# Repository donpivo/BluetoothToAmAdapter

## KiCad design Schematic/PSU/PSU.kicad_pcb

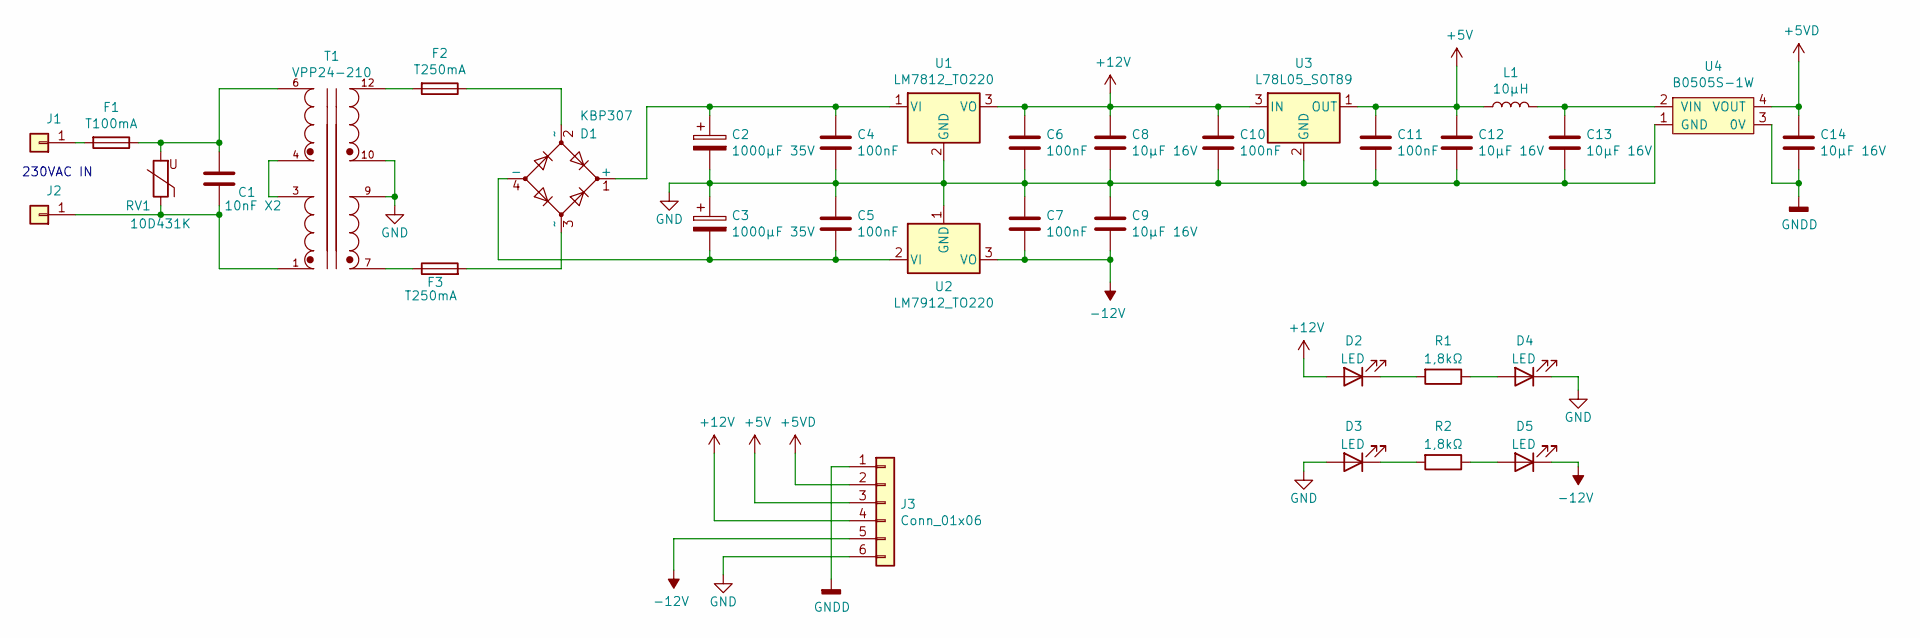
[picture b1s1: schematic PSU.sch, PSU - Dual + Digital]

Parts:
C1: 10nF X2; C_Rect_L10.3mm_W4.5mm_P7.50mm_MKS4
C2, C3: 1000µF 35V; CP_Radial_D12.5mm_P5.00mm
C4, C5, C6, C7, C10, C11: 100nF; C_0805_2012Metric_Pad1.18x1.45mm_HandSolder
C8, C9, C12, C13, C14: 10µF 16V; C_0805_2012Metric_Pad1.18x1.45mm_HandSolder
D1: KBP307; Rectifier_KBP307
D2, D3, D4, D5: LED; LED_0805_2012Metric_Pad1.15x1.40mm_HandSolder
F1: T100mA; Fuse_Littelfuse_372_D8.50mm
F2, F3: T250mA; Fuse_Littelfuse_372_D8.50mm
J1, J2: Conn_01x01; Pad_7mm
J3: Conn_01x06; KF2510-6P
L1: 10µH; L_0805_2012Metric_Pad1.15x1.40mm_HandSolder
R1, R2: 1,8kΩ; R_0805_2012Metric_Pad1.20x1.40mm_HandSolder
RV1: 10D431K; RV_Disc_D12mm_W4.3mm_P7.5mm
T1: VPP24-210; Transformer_XFMR_VPP24-210
U1: LM7812_TO220; TO-220-3_Heatsink1
U2: LM7912_TO220; TO-220-3_Heatsink1
U3: L78L05_SOT89; SOT-89-3
U4: B0505S-1W; B0505S

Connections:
+5V: C11.1, C12.1, J3.3, L1.1, U3.1 (OUT)
+5VD: C14.1, J3.2, U4.4 (VOUT)
+12V: C6.1, C8.1, C10.1, D2.2 (A), J3.4, U1.3 (VO), U3.3 (IN)
-12V: C7.2, C9.2, D5.1 (K), J3.5, U2.3 (VO)
GND: C2.2, C3.1, C4.2, C5.1, C6.2, C7.1, C8.2, C9.1, C10.2, C11.2, C12.2, C13.2, D3.2 (A), D4.1 (K), J3.6, T1.9, T1.10, U1.2 (GND), U2.1 (GND), U3.2 (GND), U4.1 (GND)
GNDD: C14.2, J3.1, U4.3 (0V)
unnamed: C1.1, F1.1, RV1.2, T1.6
unnamed: C1.2, J2.1, RV1.1, T1.1
unnamed: C2.1, C4.1, D1.1 (+), U1.1 (VI)
unnamed: C3.2, C5.2, D1.4 (-), U2.2 (VI)
unnamed: C13.1, L1.2, U4.2 (VIN)
unnamed: D1.2 (~~), F2.1
unnamed: D1.3 (~~), F3.2
unnamed: D2.1 (K), R1.2
unnamed: D3.1 (K), R2.2
unnamed: D4.2 (A), R1.1
unnamed: D5.2 (A), R2.1
unnamed: F1.2, J1.1
unnamed: F2.2, T1.12
unnamed: F3.1, T1.7
unnamed: T1.3, T1.4

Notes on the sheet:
230VAC IN

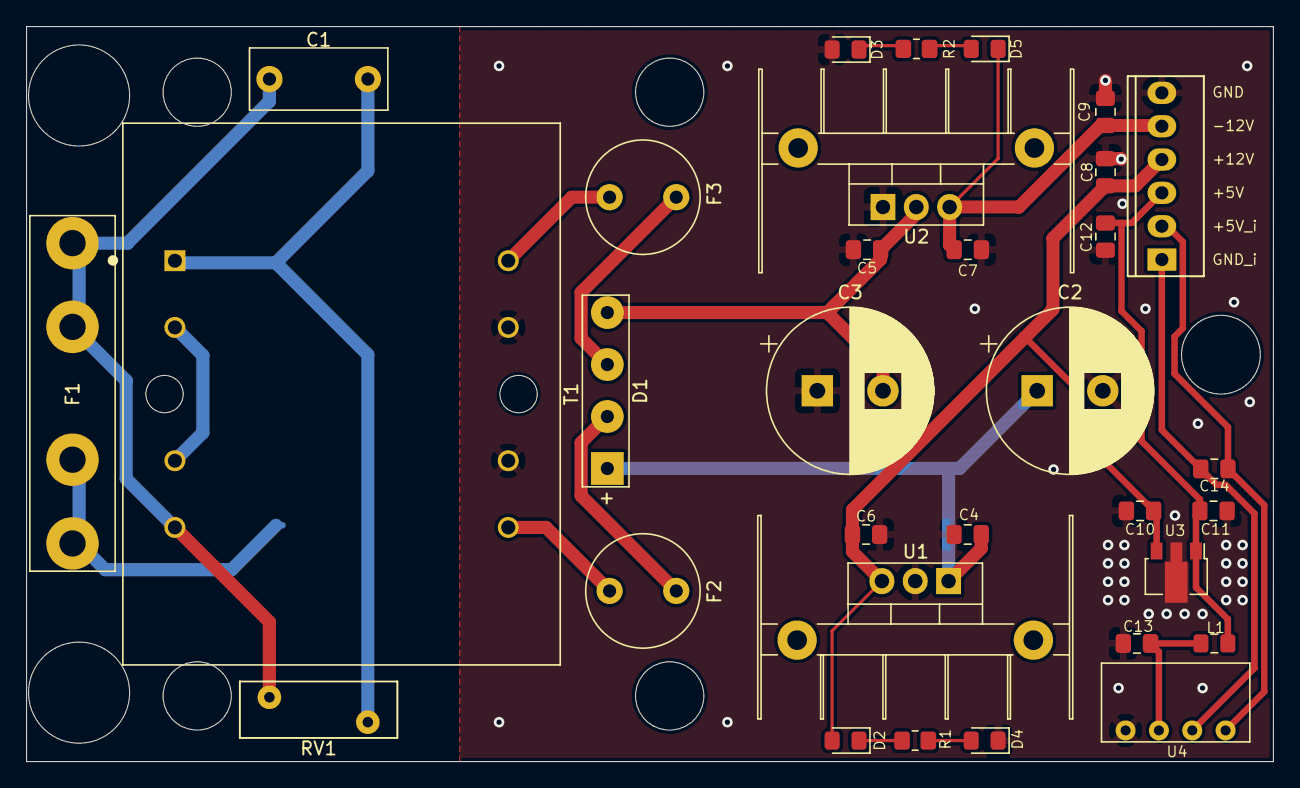
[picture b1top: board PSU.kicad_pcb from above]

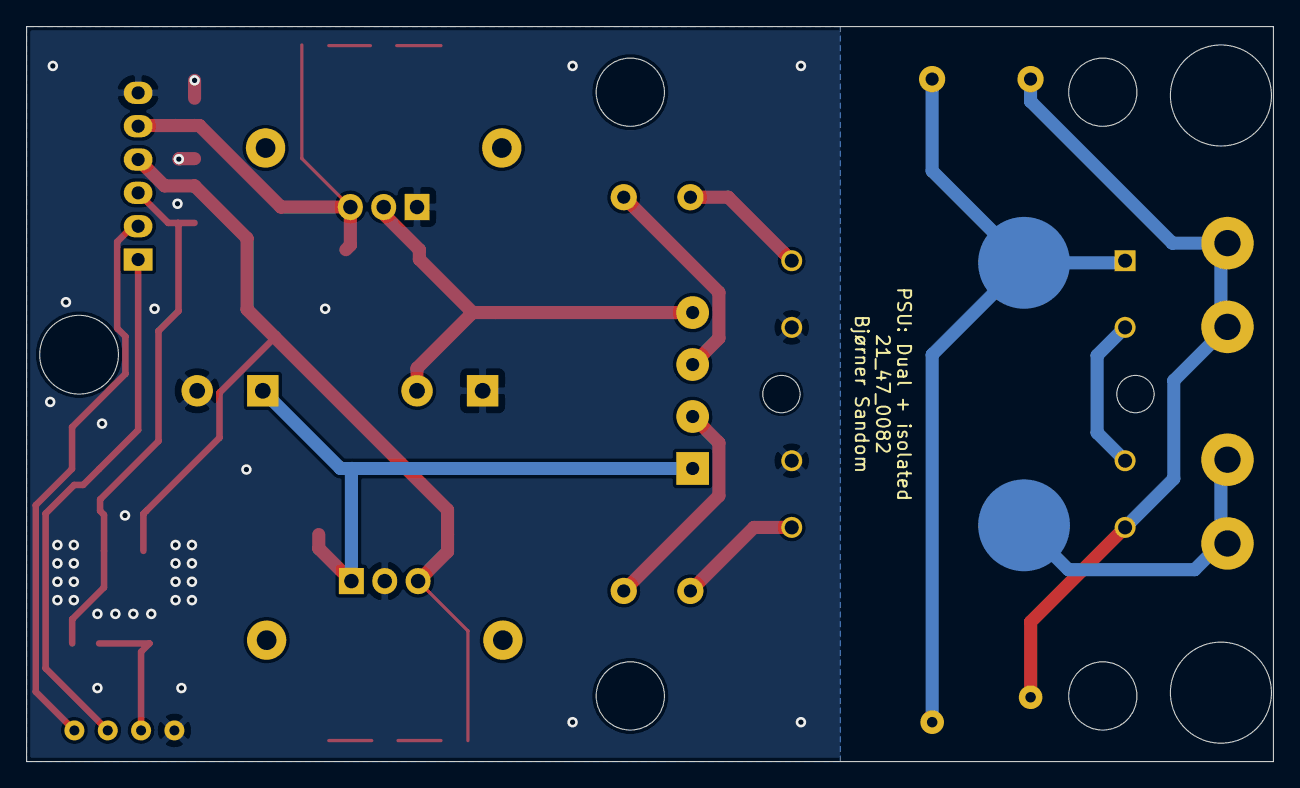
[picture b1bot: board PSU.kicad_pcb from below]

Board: 2 copper layers, 95.0 x 56.0 mm, 34 parts (2 on the bottom side), 21 nets.

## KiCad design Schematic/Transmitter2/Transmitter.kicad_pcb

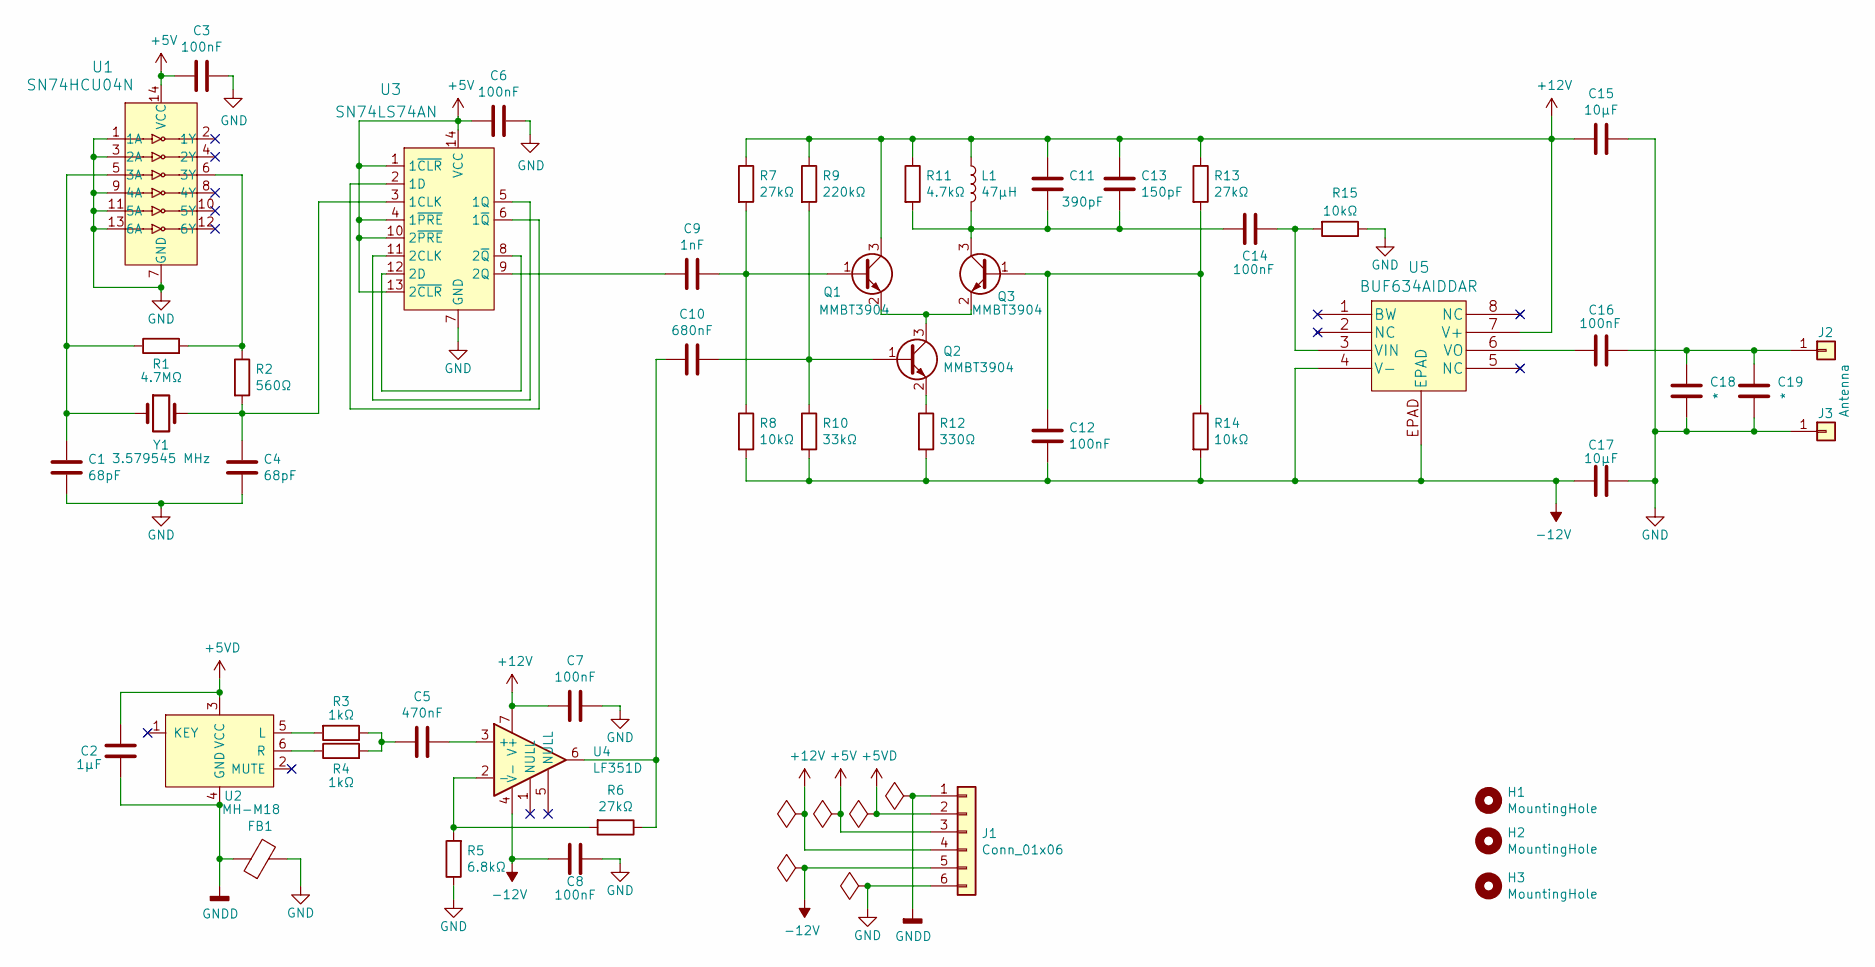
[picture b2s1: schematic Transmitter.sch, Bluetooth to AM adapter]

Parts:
C1, C4: 68pF; C_0603_1608Metric_Pad1.08x0.95mm_HandSolder
C2: 1µF; C_0603_1608Metric_Pad1.08x0.95mm_HandSolder
C3, C6, C7, C8, C12, C14, C16: 100nF; C_0603_1608Metric_Pad1.08x0.95mm_HandSolder
C5: 470nF; C_0603_1608Metric_Pad1.08x0.95mm_HandSolder
C9: 1nF; C_0603_1608Metric_Pad1.08x0.95mm_HandSolder
C10: 680nF; C_0603_1608Metric_Pad1.08x0.95mm_HandSolder
C11: 390pF; C_0603_1608Metric_Pad1.08x0.95mm_HandSolder
C13: 150pF; C_0603_1608Metric_Pad1.08x0.95mm_HandSolder
C15, C17: 10µF; C_0603_1608Metric_Pad1.08x0.95mm_HandSolder
C18, C19: *; C_0603_1608Metric_Pad1.08x0.95mm_HandSolder
FB1: Ferrite_Bead; L_0805_2012Metric_Pad1.15x1.40mm_HandSolder
H1, H2, H3: MountingHole; MountingHole_3.2mm_M3
J1: Conn_01x06; PinHeader_1x06_P2.54mm_Vertical
J2: Antenna; Pin_D1.3mm_L11.0mm_LooseFit
J3: Conn_01x01; Pin_D1.3mm_L11.0mm_LooseFit
L1: 47µH; L_0805_2012Metric_Pad1.15x1.40mm_HandSolder
Q1, Q2, Q3: MMBT3904; SOT-23
R1: 4.7MΩ; R_0603_1608Metric_Pad1.05x0.95mm_HandSolder
R2: 560Ω; R_0603_1608Metric_Pad1.05x0.95mm_HandSolder
R3, R4: 1kΩ; R_0603_1608Metric_Pad1.05x0.95mm_HandSolder
R5: 6.8kΩ; R_0603_1608Metric_Pad1.05x0.95mm_HandSolder
R6, R7, R13: 27kΩ; R_0603_1608Metric_Pad1.05x0.95mm_HandSolder
R8, R14, R15: 10kΩ; R_0603_1608Metric_Pad1.05x0.95mm_HandSolder
R9: 220kΩ; R_0603_1608Metric_Pad1.05x0.95mm_HandSolder
R10: 33kΩ; R_0603_1608Metric_Pad1.05x0.95mm_HandSolder
R11: 4.7kΩ; R_0603_1608Metric_Pad1.05x0.95mm_HandSolder
R12: 330Ω; R_0603_1608Metric_Pad1.05x0.95mm_HandSolder
U1: SN74HCU04N; TSSOP-14_4.4x5mm_P0.65mm; MPN SN74HC04N; Digi-Key_PN 296-1566-5-ND
U2: MH-M18
U3: SN74LS74AN; SOIC-14_3.9x8.7mm_P1.27mm; MPN SN74LS74AN; Digi-Key_PN 296-1668-5-ND
U4: LF351D; SO-8_5.3x6.2mm_P1.27mm
U5: BUF634AIDDAR; SOIC-8-1EP_3.9x4.9mm_P1.27mm_EP2.514x3.2mm_ThermalVias
Y1: 3.579545 MHz; Crystal_SMD_HC49-SD

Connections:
+5V: C3.2, C6.2, J1.3, U1.14 (VCC), U3.1 (1~CLR), U3.4 (1~PRE), U3.10 (2~PRE), U3.13 (2~CLR), U3.14 (VCC)
+5VD: C2.1, J1.2, U2.3 (VCC)
+12V: C7.2, C11.1, C13.1, C15.2, J1.4, L1.1, Q1.3 (C), R7.1, R9.1, R11.1, R13.1, U4.7 (V+), U5.7 (V+)
-12V: C8.2, C12.2, C17.2, J1.5, R8.2, R10.2, R12.2, R14.2, U4.4 (V-), U5.4 (V-), U5.EPAD
GND: C1.2, C3.1, C4.2, C6.1, C7.1, C8.1, C15.1, C17.1, C18.2, C19.2, FB1.2, J1.6, J3.1, R5.1, R15.1, U1.1 (1A), U1.3 (2A), U1.7 (GND), U1.9 (4A), U1.11 (5A), U1.13 (6A), U3.7 (GND)
GNDD: C2.2, FB1.1, J1.1, U2.4 (GND)
unnamed: C1.1, R1.1, U1.5 (3A), Y1.1
unnamed: C4.1, R2.2, U3.3 (1CLK), Y1.2
unnamed: C5.1, U4.3 (+)
unnamed: C5.2, R3.1, R4.2
unnamed: C9.1, Q1.1 (B), R7.2, R8.1
unnamed: C9.2, U3.9 (2Q)
unnamed: C10.1, Q2.1 (B), R9.2, R10.1
unnamed: C10.2, R6.1, U4.6
unnamed: C11.2, C13.2, C14.2, L1.2, Q3.3 (C), R11.2
unnamed: C12.1, Q3.1 (B), R13.2, R14.1
unnamed: C14.1, R15.2, U5.3 (VIN)
unnamed: C16.1, C18.1, C19.1, J2.1
unnamed: C16.2, U5.6 (VO)
unnamed: Q1.2 (E), Q2.3 (C), Q3.2 (E)
unnamed: Q2.2 (E), R12.1
unnamed: R1.2, R2.1, U1.6 (3Y)
unnamed: R3.2, U2.5 (L)
unnamed: R4.1, U2.6 (R)
unnamed: R5.2, R6.2, U4.2 (-)
unnamed: U3.2 (1D), U3.6 (1~Q)
unnamed: U3.5 (1Q), U3.11 (2CLK)
unnamed: U3.8 (2~Q), U3.12 (2D)

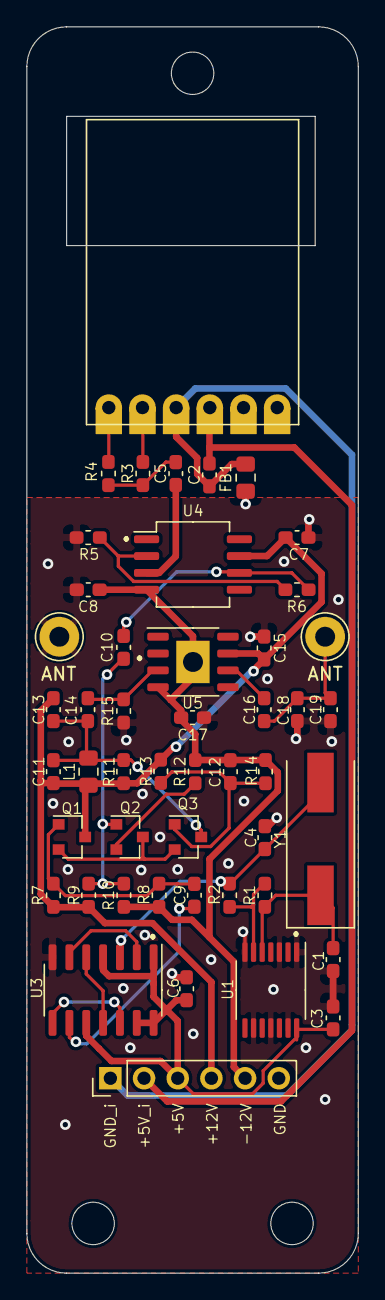
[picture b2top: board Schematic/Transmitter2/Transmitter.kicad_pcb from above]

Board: 2 copper layers, 25.0 x 94.0 mm, 51 parts (0 on the bottom side), 28 nets.

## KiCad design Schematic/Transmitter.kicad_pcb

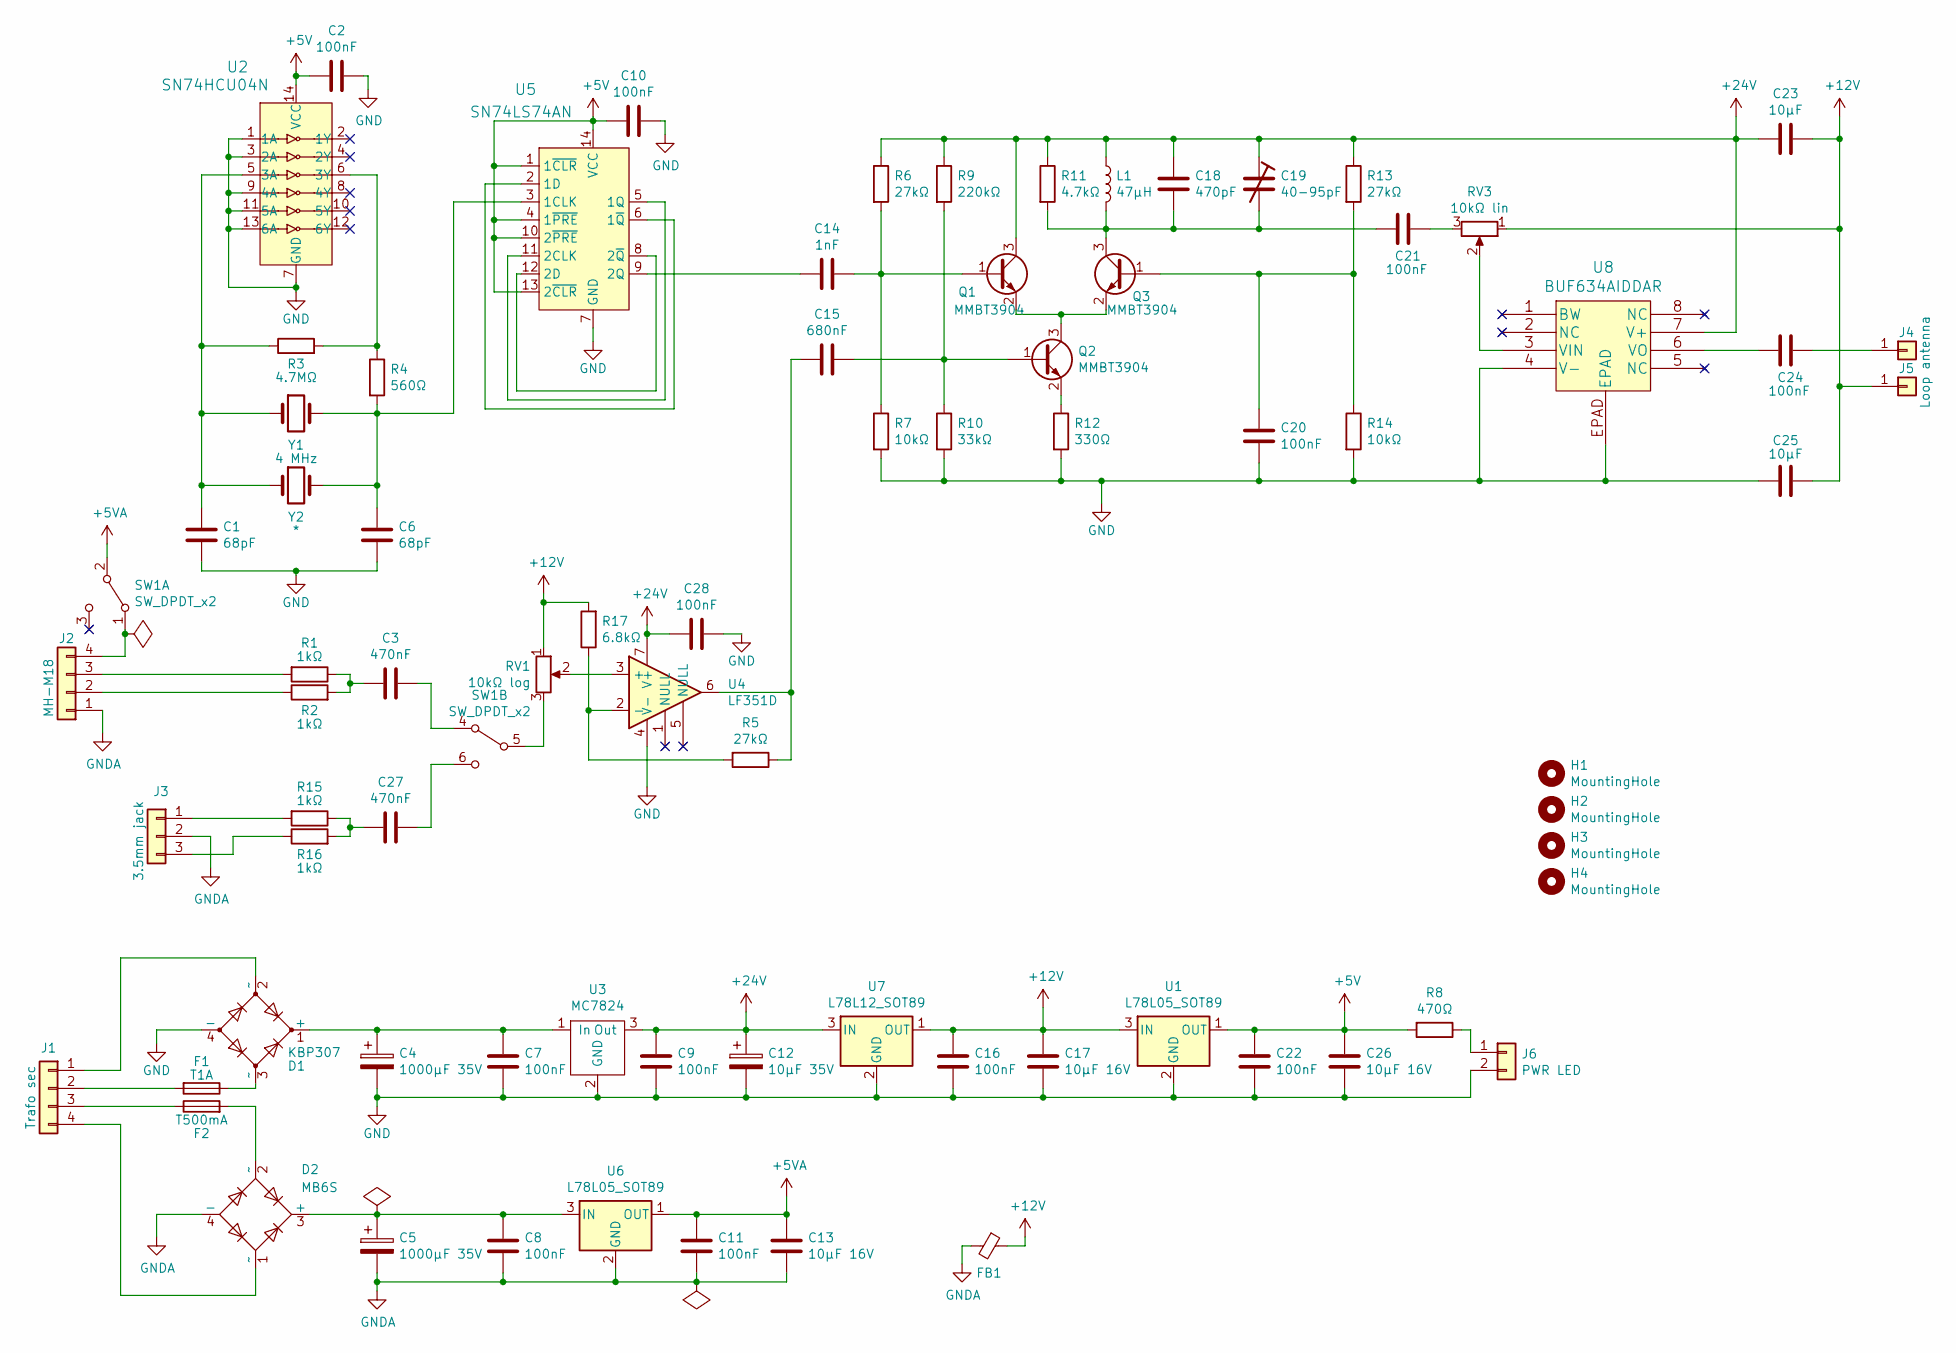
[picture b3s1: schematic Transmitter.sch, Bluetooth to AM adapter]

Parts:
C1, C6: 68pF; C_0603_1608Metric_Pad1.08x0.95mm_HandSolder
C2, C7, C8, C9, C10, C11, C16, C20, C21, C22, C24, C28: 100nF; C_0603_1608Metric_Pad1.08x0.95mm_HandSolder
C3, C27: 470nF; C_0603_1608Metric_Pad1.08x0.95mm_HandSolder
C4, C5: 1000µF 35V; CP_Radial_D12.5mm_P5.00mm
C12: 10µF 35V; CP_Elec_4x5.4
C13, C17, C26: 10µF 16V; C_0603_1608Metric_Pad1.08x0.95mm_HandSolder
C14: 1nF; C_0603_1608Metric_Pad1.08x0.95mm_HandSolder
C15: 680nF; C_0603_1608Metric_Pad1.08x0.95mm_HandSolder
C18: 470pF; C_0603_1608Metric_Pad1.08x0.95mm_HandSolder
C19: 40-95pF; Trimmer_cap_THT_7mm
C23, C25: 10µF; C_0603_1608Metric_Pad1.08x0.95mm_HandSolder
D1: KBP307; Rectifier_KBP307
D2: MB6S; TO-269AA
F1: T1A; Fuse_Littelfuse_372_D8.50mm
F2: T500mA; Fuse_Littelfuse_372_D8.50mm
FB1: Ferrite_Bead_Small; L_0805_2012Metric_Pad1.15x1.40mm_HandSolder
H1, H2, H3, H4: MountingHole; MountingHole_3.2mm_M3
J1: Trafo sec; KF2510-4P
J2: MH-M18; PinHeader_1x04_P2.54mm_Vertical
J3: 3.5mm jack; KF2510-3P
J4: Loop antenna; Pin_D1.3mm_L11.0mm_LooseFit
J5: Conn_01x01; Pin_D1.3mm_L11.0mm_LooseFit
J6: PWR LED; PinHeader_1x02_P2.54mm_Vertical
L1: 47µH; L_0805_2012Metric_Pad1.15x1.40mm_HandSolder
Q1, Q2, Q3: MMBT3904; SOT-23
R1, R2, R15, R16: 1kΩ; R_0603_1608Metric_Pad1.05x0.95mm_HandSolder
R3: 4.7MΩ; R_0603_1608Metric_Pad1.05x0.95mm_HandSolder
R4: 560Ω; R_0603_1608Metric_Pad1.05x0.95mm_HandSolder
R5, R6, R13: 27kΩ; R_0603_1608Metric_Pad1.05x0.95mm_HandSolder
R7, R14: 10kΩ; R_0603_1608Metric_Pad1.05x0.95mm_HandSolder
R8: 470Ω; R_0603_1608Metric_Pad1.05x0.95mm_HandSolder
R9: 220kΩ; R_0603_1608Metric_Pad1.05x0.95mm_HandSolder
R10: 33kΩ; R_0603_1608Metric_Pad1.05x0.95mm_HandSolder
R11: 4.7kΩ; R_0603_1608Metric_Pad1.05x0.95mm_HandSolder
R12: 330Ω; R_0603_1608Metric_Pad1.05x0.95mm_HandSolder
R17: 6.8kΩ; R_0603_1608Metric_Pad1.05x0.95mm_HandSolder
RV1: 10kΩ log; Potentiometer_Alps_RK163_Single_Horizontal
RV3: 10kΩ lin; Potentiometer_Alps_RK163_Single_Horizontal
SW1: SW_DPDT_x2; Toggle_sw_submin
U1, U6: L78L05_SOT89; SOT-89-3
U2: SN74HCU04N; TSSOP-14_4.4x5mm_P0.65mm; MPN SN74HC04N; Digi-Key_PN 296-1566-5-ND
U3: MC7824; TO-263-2
U4: LF351D; SO-8_5.3x6.2mm_P1.27mm
U5: SN74LS74AN; SOIC-14_3.9x8.7mm_P1.27mm; MPN SN74LS74AN; Digi-Key_PN 296-1668-5-ND
U7: L78L12_SOT89; SOT-89-3
U8: BUF634AIDDAR; SOIC-8-1EP_3.9x4.9mm_P1.27mm_EP2.514x3.2mm_ThermalVias
Y1: 4 MHz; Crystal_HC49-U_Vertical
Y2: *; Crystal_SMD_HC49-SD

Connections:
+5V: C2.2, C10.2, C22.1, C26.1, R8.2, U1.1 (OUT), U2.14 (VCC), U5.1 (1~CLR), U5.4 (1~PRE), U5.10 (2~PRE), U5.13 (2~CLR), U5.14 (VCC)
+5VA: C11.1, C13.1, SW1.2 (B), U6.1 (OUT)
+12V: C16.1, C17.1, C23.1, C25.1, FB1.1, J5.1, R17.2, RV1.1, RV3.1, U1.3 (IN), U7.1 (OUT)
+24V: C9.1, C12.1, C18.1, C19.1, C23.2, C28.2, L1.1, Q1.3 (C), R6.1, R9.1, R11.1, R13.1, U3.3 (Out), U4.7 (V+), U7.3 (IN), U8.7 (V+)
GND: C1.2, C2.1, C4.2, C6.2, C7.2, C9.2, C10.1, C12.2, C16.2, C17.2, C20.2, C22.2, C25.2, C26.2, C28.1, D1.4 (-), J6.2, R7.2, R10.2, R12.2, R14.2, U1.2 (GND), U2.1 (1A), U2.3 (2A), U2.7 (GND), U2.9 (4A), U2.11 (5A), U2.13 (6A), U3.2 (GND), U4.4 (V-), U5.7 (GND), U7.2 (GND), U8.4 (V-), U8.EPAD
GNDA: C5.2, C8.2, C11.2, C13.2, D2.4 (-), FB1.2, J2.1, J3.2, U6.2 (GND)
unnamed: C1.1, R3.1, U2.5 (3A), Y1.1, Y2.1
unnamed: C3.1, SW1.4 (A)
unnamed: C3.2, R1.1, R2.2
unnamed: C4.1, C7.1, D1.1 (+), U3.1 (In)
unnamed: C5.1, C8.1, D2.3 (+), U6.3 (IN)
unnamed: C6.1, R4.2, U5.3 (1CLK), Y1.2, Y2.2
unnamed: C14.1, Q1.1 (B), R6.2, R7.1
unnamed: C14.2, U5.9 (2Q)
unnamed: C15.1, Q2.1 (B), R9.2, R10.1
unnamed: C15.2, R5.1, U4.6
unnamed: C18.2, C19.2, C21.2, L1.2, Q3.3 (C), R11.2
unnamed: C20.1, Q3.1 (B), R13.2, R14.1
unnamed: C21.1, RV3.3
unnamed: C24.1, J4.1
unnamed: C24.2, U8.6 (VO)
unnamed: C27.1, SW1.6 (C)
unnamed: C27.2, R15.1, R16.2
unnamed: D1.2 (~~), J1.1
unnamed: D1.3 (~~), F1.1
unnamed: D2.1 (~~), J1.4
unnamed: D2.2 (~~), F2.2
unnamed: F1.2, J1.2
unnamed: F2.1, J1.3
unnamed: J2.2, R2.1
unnamed: J2.3, R1.2
unnamed: J2.4, SW1.1 (A)
unnamed: J3.1, R15.2
unnamed: J3.3, R16.1
unnamed: J6.1, R8.1
unnamed: Q1.2 (E), Q2.3 (C), Q3.2 (E)
unnamed: Q2.2 (E), R12.1
unnamed: R3.2, R4.1, U2.6 (3Y)
unnamed: R5.2, R17.1, U4.2 (-)
unnamed: RV1.2, U4.3 (+)
unnamed: RV1.3, SW1.5 (B)
unnamed: RV3.2, U8.3 (VIN)
unnamed: U5.2 (1D), U5.6 (1~Q)
unnamed: U5.5 (1Q), U5.11 (2CLK)
unnamed: U5.8 (2~Q), U5.12 (2D)

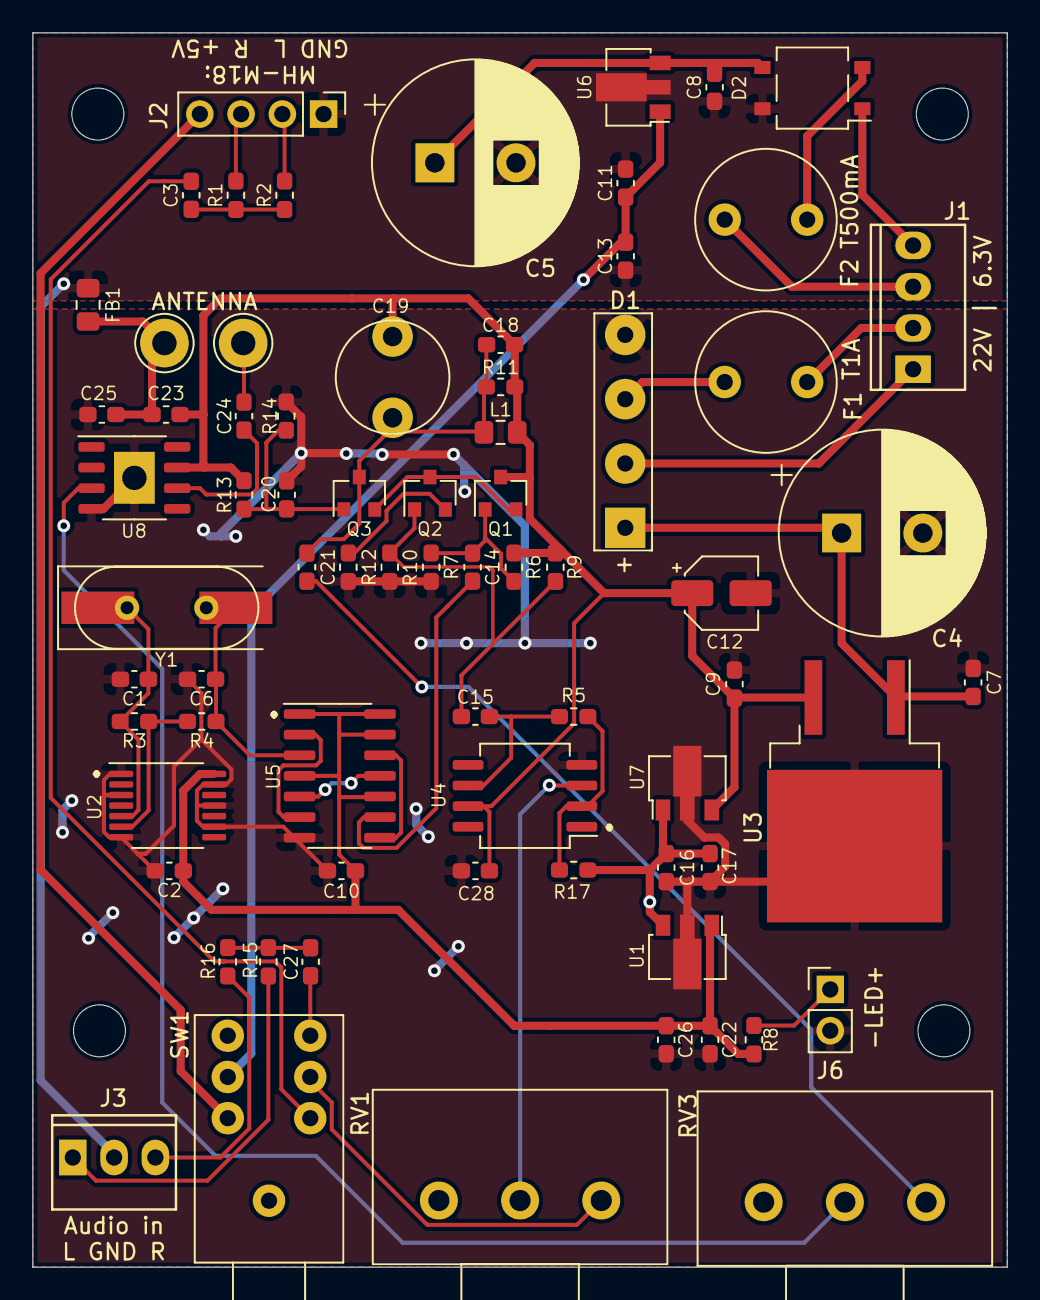
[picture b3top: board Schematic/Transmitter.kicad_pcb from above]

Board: 2 copper layers, 60.0 x 76.0 mm, 77 parts (0 on the bottom side), 45 nets.

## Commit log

2021-11-08 Created repository
2021-11-26 New compact version with separate PSU
2021-12-21 Added missing resistor: R15
